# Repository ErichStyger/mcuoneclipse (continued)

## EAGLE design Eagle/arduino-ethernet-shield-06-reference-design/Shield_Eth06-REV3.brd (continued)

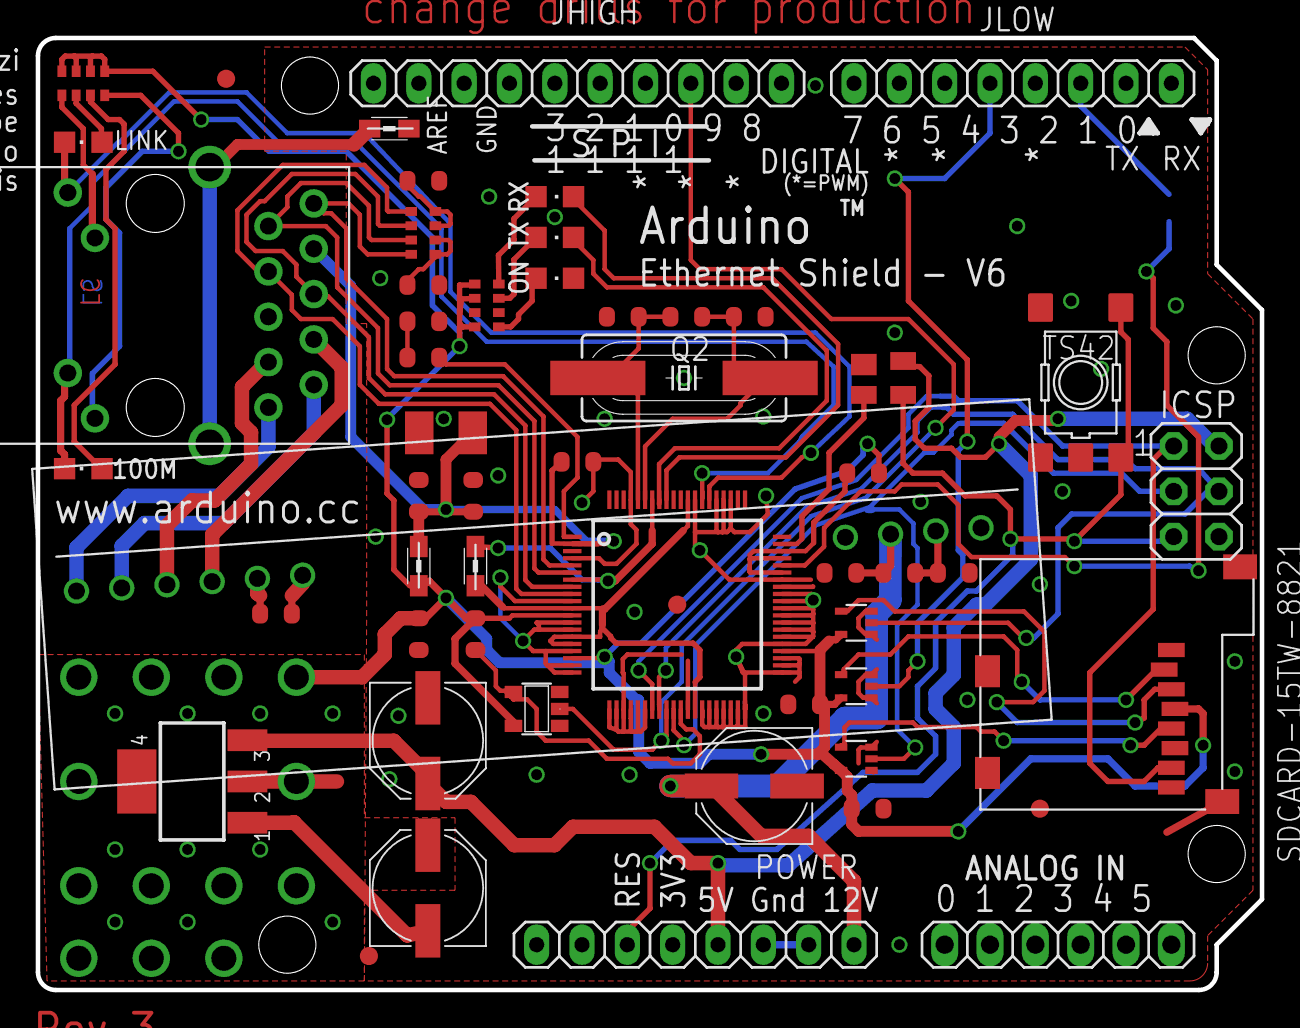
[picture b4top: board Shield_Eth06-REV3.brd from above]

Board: 2 copper layers, 68.6 x 53.3 mm, 57 parts (1 on the bottom side), 50 nets.

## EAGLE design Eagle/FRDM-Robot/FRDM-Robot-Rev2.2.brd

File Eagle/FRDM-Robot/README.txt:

Freedom Robot Board Rev. 2.2
============================

- Schema Änderungen:
  - Ultraschall Speisung auf 5V
  - Bluetooth TX/RX korrigiert

- Änderungen im Layout NICHT GEROUTET!!!

Andrin Tuor, 27.6.2013

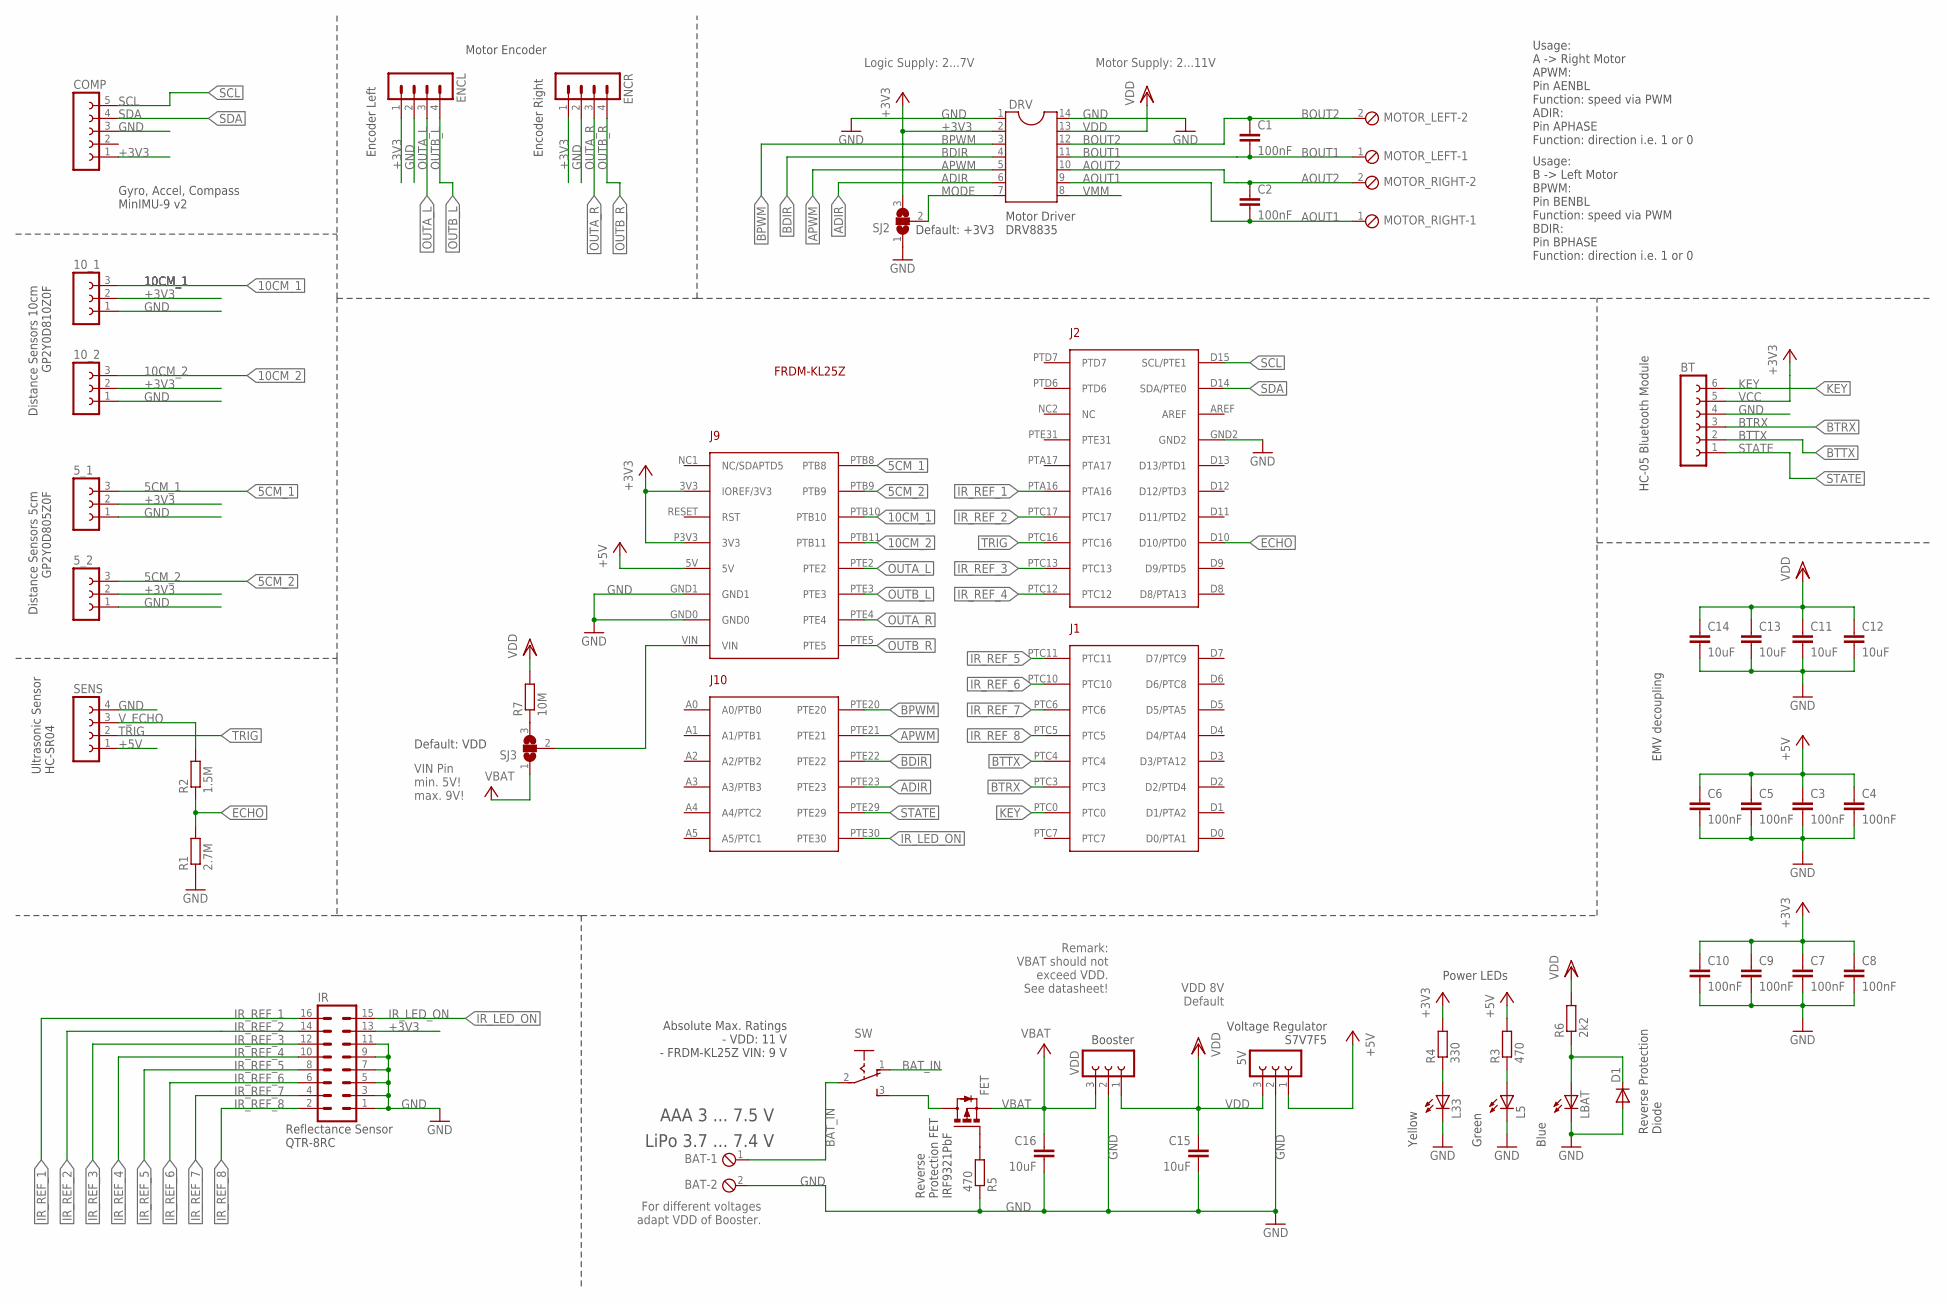
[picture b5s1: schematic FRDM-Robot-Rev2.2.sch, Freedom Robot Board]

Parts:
5V, 5_1, 5_2, 10_1, 10_2: FE03-1
BAT: MPT2; 2POL254
BT: FE06-1; FE06
C1, C2, C3, C4, C5, C6, C7, C8, C9, C10: 100nF; C0805
C11, C12, C13, C14, C15, C16: 10uF; C0805
COMP: FE05-1
D1: DIODE-SOD123; SOD123
DRV: DIL14
ENCL: MA04-1
ENCR: MA04-1
FET: P-MOSFET-SO8; SO-08
FRDM1: FRDM-KL25ZARDUINO; FRDM-KL25Z
IR: MA08-2
L5, L33: LEDCHIP-LED0603; CHIP-LED0603
LBAT: LEDCHIP-LED0603; CHIP-LED0603
MOTOR_LEFT: MPT2; 2POL254
MOTOR_RIGHT: MPT2; 2POL254
R1: 2.7M; M0805
R2: 1.5M; M0805
R3, R5: 470; M0805
R4: 330; M0805
R6: 2k2; M0805
R7: 10M; M0805
SENS: FE04-1
SJ2, SJ3: SJ2W; SJ_2
SW: KNITTER-MFP106D
VDD: FE03-1

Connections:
5CM_1: 5_1.3, FRDM1.PTB8
5CM_2: 5_2.3, FRDM1.PTB9
10CM_1: 10_1.3, FRDM1.PTB10
10CM_2: 10_2.3, FRDM1.PTB11
+3V3: 5_1.2, 5_2.2, 10_1.2, 10_2.2, C7.1, C8.1, C9.1, C10.1, COMP.1, DRV.2, ENCL.1, ENCR.1, FRDM1.3V3 (IOREF/3V3), FRDM1.P3V3 (3V3), IR.13, R4.2, SJ2.3
+5V: 5V.1, C3.1, C4.1, C5.1, C6.1, FRDM1.5V, R3.2, SENS.1
ADIR: DRV.6, FRDM1.PTE23
AOUT1: C2.2, DRV.9, MOTOR_RIGHT.1
AOUT2: C2.1, DRV.10, MOTOR_RIGHT.2
APWM: DRV.5, FRDM1.PTE21
BAT-FET: FET.5 (D), FET.6 (D), FET.7 (D), FET.8 (D), SW.3 (S)
BAT_IN: BAT.1, SW.1 (O), SW.2
BDIR: DRV.4, FRDM1.PTE22
BOUT1: C1.2, DRV.11, MOTOR_LEFT.1
BOUT2: C1.1, DRV.12, MOTOR_LEFT.2
BPWM: DRV.3, FRDM1.PTE20
BTRX: BT.3, FRDM1.PTC3
BTTX: BT.2, FRDM1.PTC4
ECHO: FRDM1.D10 (D10/PTD0), R1.2, R2.1
GND: 5V.2, 5_1.1, 5_2.1, 10_1.1, 10_2.1, BAT.2, BT.4, C3.2, C4.2, C5.2, C6.2, C7.2, C8.2, C9.2, C10.2, C11.2, C12.2, C13.2, C14.2, C15.2, C16.2, COMP.3, D1.A, DRV.1, DRV.14, ENCL.2, ENCR.2, FRDM1.GND0, FRDM1.GND1, FRDM1.GND2, IR.1, IR.3, IR.5, IR.7, IR.9, IR.11, L5.C, L33.C, LBAT.C, R1.1, R5.1, SENS.4, SJ2.1, VDD.2
IR_LED_ON: FRDM1.PTE30, IR.15
IR_REF_1: FRDM1.PTA16, IR.16
IR_REF_2: FRDM1.PTC17, IR.14
IR_REF_3: FRDM1.PTC13, IR.12
IR_REF_4: FRDM1.PTC12, IR.10
IR_REF_5: FRDM1.PTC11, IR.8
IR_REF_6: FRDM1.PTC10, IR.6
IR_REF_7: FRDM1.PTC6, IR.4
IR_REF_8: FRDM1.PTC5, IR.2
KEY: BT.6, FRDM1.PTC0
MODE: DRV.7, SJ2.2
unnamed: L5.A, R3.1
unnamed: R7.1, SJ3.3
unnamed: L33.A, R4.1
unnamed: FET.4 (G), R5.2
unnamed: D1.C, LBAT.A, R6.1
OUTA_L: ENCL.3, FRDM1.PTE2
OUTA_R: ENCR.3, FRDM1.PTE4
OUTB_L: ENCL.4, FRDM1.PTE3
OUTB_R: ENCR.4, FRDM1.PTE5
SCL: COMP.5, FRDM1.D15 (SCL/PTE1)
SDA: COMP.4, FRDM1.D14 (SDA/PTE0)
STATE: BT.1, FRDM1.PTE29
TRIG: FRDM1.PTC16, SENS.2
VBAT: C16.1, FET.1 (S), FET.2 (S), FET.3 (S), SJ3.1, VDD.3
VCC: BT.5
VDD: 5V.3, C11.1, C12.1, C13.1, C14.1, C15.1, DRV.13, R6.2, R7.2, VDD.1
VIN: FRDM1.VIN, SJ3.2
VMM: DRV.8
V_ECHO: R2.2, SENS.3

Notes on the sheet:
Distance Sensors 10cm GP2Y0D810Z0F
Ultrasonic Sensor HC-SR04
Motor Encoder
Motor Driver DRV8835
Reflectance Sensor QTR-8RC
Voltage Regulator S7V7F5
HC-05 Bluetooth Module
Reverse Protection FET IRF9321PbF
LiPo 3.7 ... 7.4 V
Usage: A -> Right Motor APWM: Pin AENBL Function: speed via PWM ADIR: Pin APHASE Function: direction i.e. 1 or 0
Distance Sensors 5cm GP2Y0D805Z0F
EMV decoupling
Power LEDs
Motor Supply: 2...11V
Logic Supply: 2...7V
Remark: VBAT should not exceed VDD. See datasheet!
For different voltages adapt VDD of Booster.
Usage: B -> Left Motor BPWM: Pin BENBL Function: speed via PWM BDIR: Pin BPHASE Function: direction i.e. 1 or 0
Reverse Protection Diode
VIN Pin min. 5V! max. 9V!
VDD 8V Default
Gyro, Accel, Compass MinIMU-9 v2
AAA 3 ... 7.5 V
Absolute Max. Ratings - VDD: 11 V - FRDM-KL25Z VIN: 9 V
Encoder Left
Encoder Right
Booster
Yellow
Green
Blue
Default: +3V3
Default: VDD

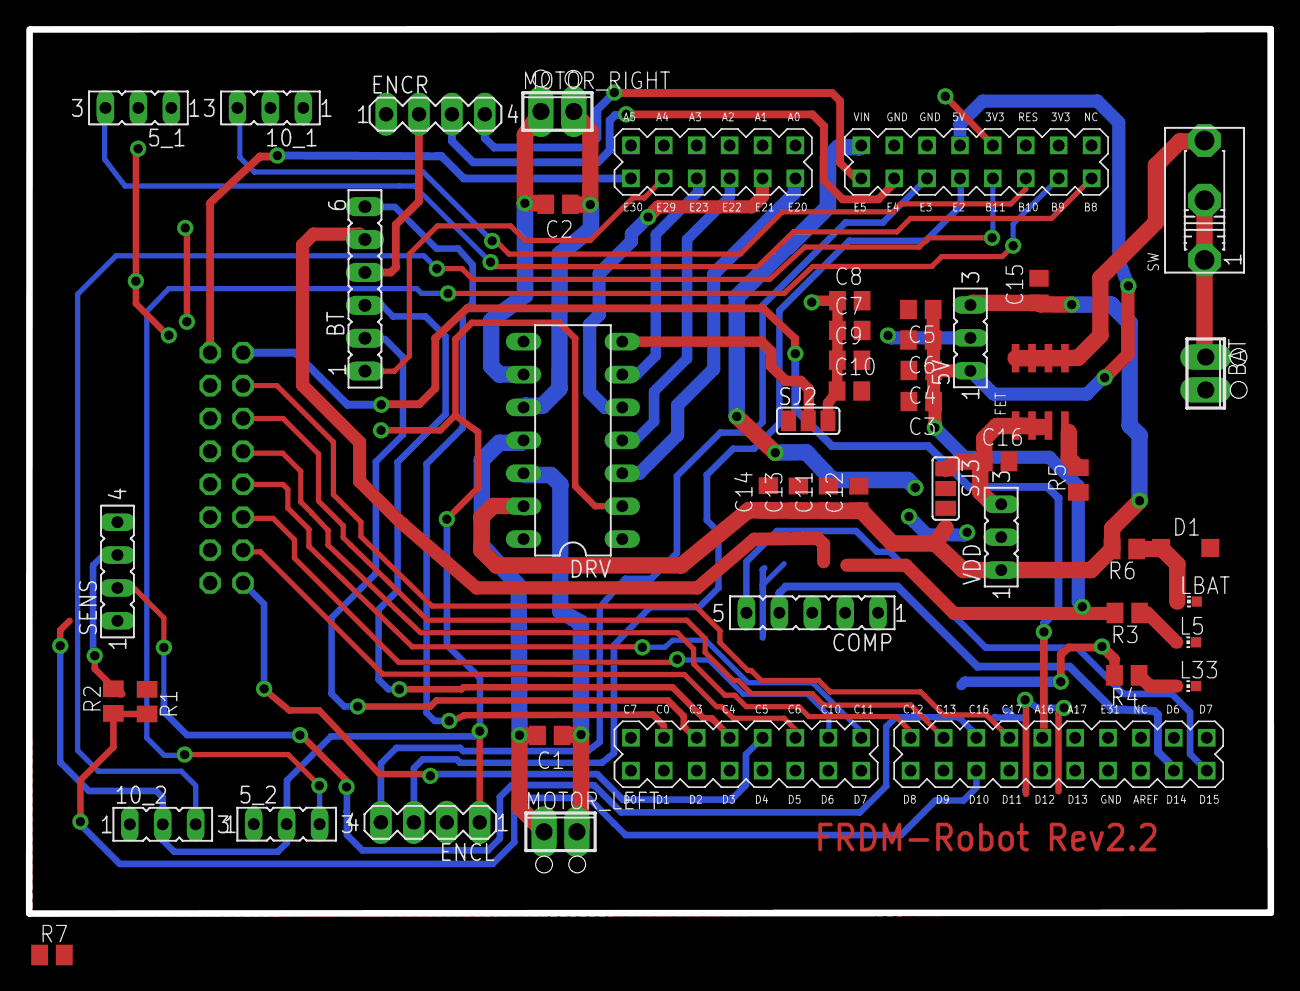
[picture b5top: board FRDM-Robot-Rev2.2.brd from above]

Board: 2 copper layers, 95.8 x 68.3 mm, 48 parts (1 on the bottom side), 48 nets.

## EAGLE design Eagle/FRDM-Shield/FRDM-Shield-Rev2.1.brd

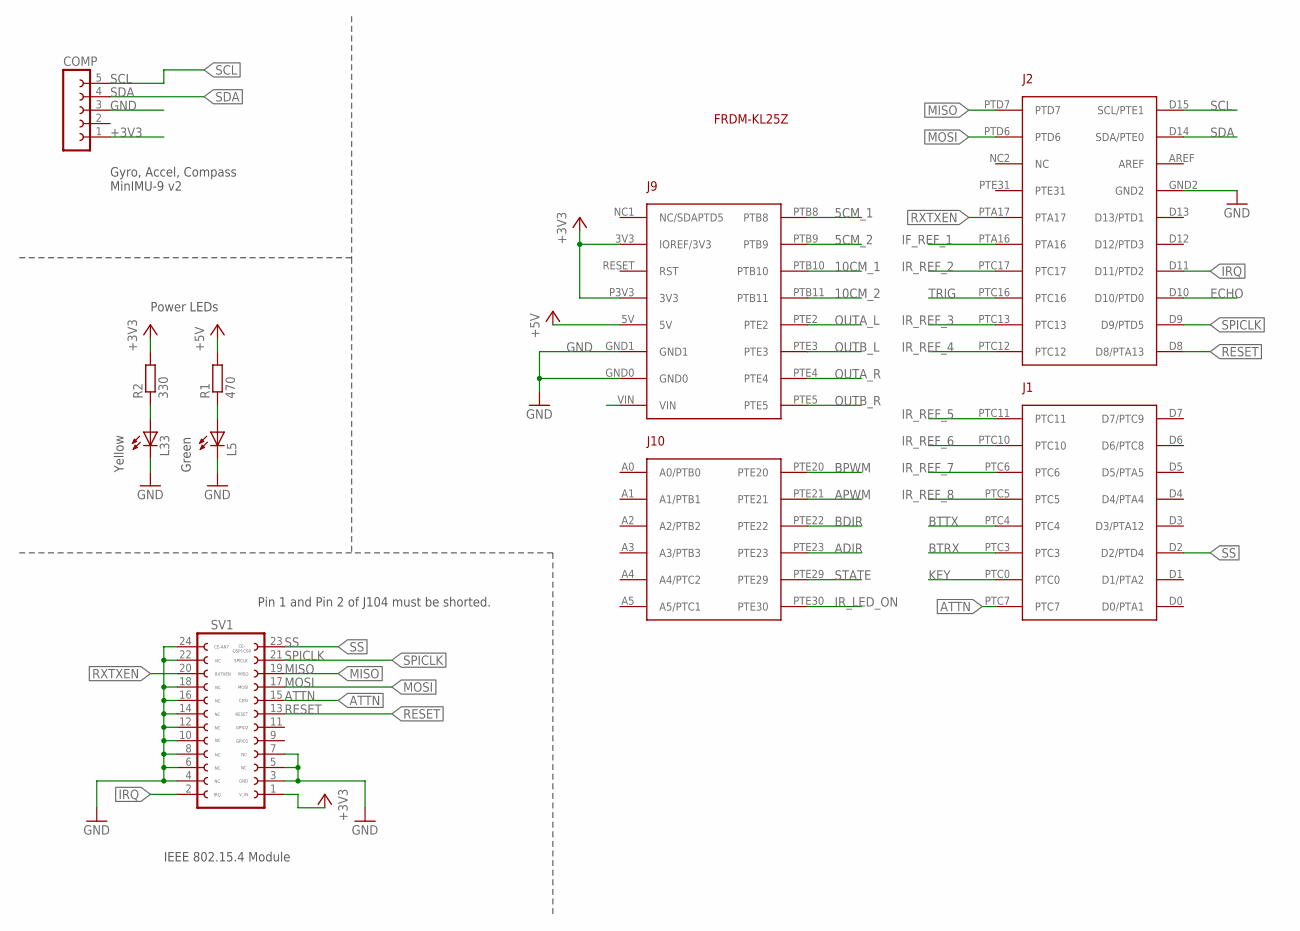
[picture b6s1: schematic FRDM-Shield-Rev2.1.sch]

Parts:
COMP: FE05-1
FRDM1: FRDM-KL25ZARDUINO; FRDM-KL25Z
L5, L33: LEDCHIP-LED0603; CHIP-LED0603
R1: 470; M0805
R2: 330; M0805
SV1: MC1320X; FE12-2

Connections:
5CM_1: FRDM1.PTB8
5CM_2: FRDM1.PTB9
10CM_1: FRDM1.PTB10
10CM_2: FRDM1.PTB11
+3V3: COMP.1, FRDM1.3V3 (IOREF/3V3), FRDM1.P3V3 (3V3), R2.2, SV1.1
+5V: FRDM1.5V, R1.2
ADIR: FRDM1.PTE23
APWM: FRDM1.PTE21
ATTN: FRDM1.PTC7, SV1.15
BDIR: FRDM1.PTE22
BPWM: FRDM1.PTE20
BTRX: FRDM1.PTC3
BTTX: FRDM1.PTC4
ECHO: FRDM1.D10 (D10/PTD0)
GND: COMP.3, FRDM1.GND0, FRDM1.GND1, FRDM1.GND2, L5.C, L33.C, SV1.3, SV1.4, SV1.5, SV1.6, SV1.7, SV1.8, SV1.10, SV1.12, SV1.14, SV1.16, SV1.18, SV1.22, SV1.24
IF_REF_1: FRDM1.PTA16
IRQ: FRDM1.D11 (D11/PTD2), SV1.2
IR_LED_ON: FRDM1.PTE30
IR_REF_2: FRDM1.PTC17
IR_REF_3: FRDM1.PTC13
IR_REF_4: FRDM1.PTC12
IR_REF_5: FRDM1.PTC11
IR_REF_6: FRDM1.PTC10
IR_REF_7: FRDM1.PTC6
IR_REF_8: FRDM1.PTC5
KEY: FRDM1.PTC0
MISO: FRDM1.PTD7, SV1.19
MOSI: FRDM1.PTD6, SV1.17
unnamed: L5.A, R1.1
unnamed: L33.A, R2.1
OUTA_L: FRDM1.PTE2
OUTA_R: FRDM1.PTE4
OUTB_L: FRDM1.PTE3
OUTB_R: FRDM1.PTE5
RESET: FRDM1.D8 (D8/PTA13), SV1.13
RXTXEN: FRDM1.PTA17, SV1.20
SCL: COMP.5, FRDM1.D15 (SCL/PTE1)
SDA: COMP.4, FRDM1.D14 (SDA/PTE0)
SPICLK: FRDM1.D9 (D9/PTD5), SV1.21
SS: FRDM1.D2 (D2/PTD4), SV1.23
STATE: FRDM1.PTE29
TRIG: FRDM1.PTC16

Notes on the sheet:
IEEE 802.15.4 Module
Power LEDs
Pin 1 and Pin 2 of J104 must be shorted.
Yellow
Green
Gyro, Accel, Compass MinIMU-9 v2

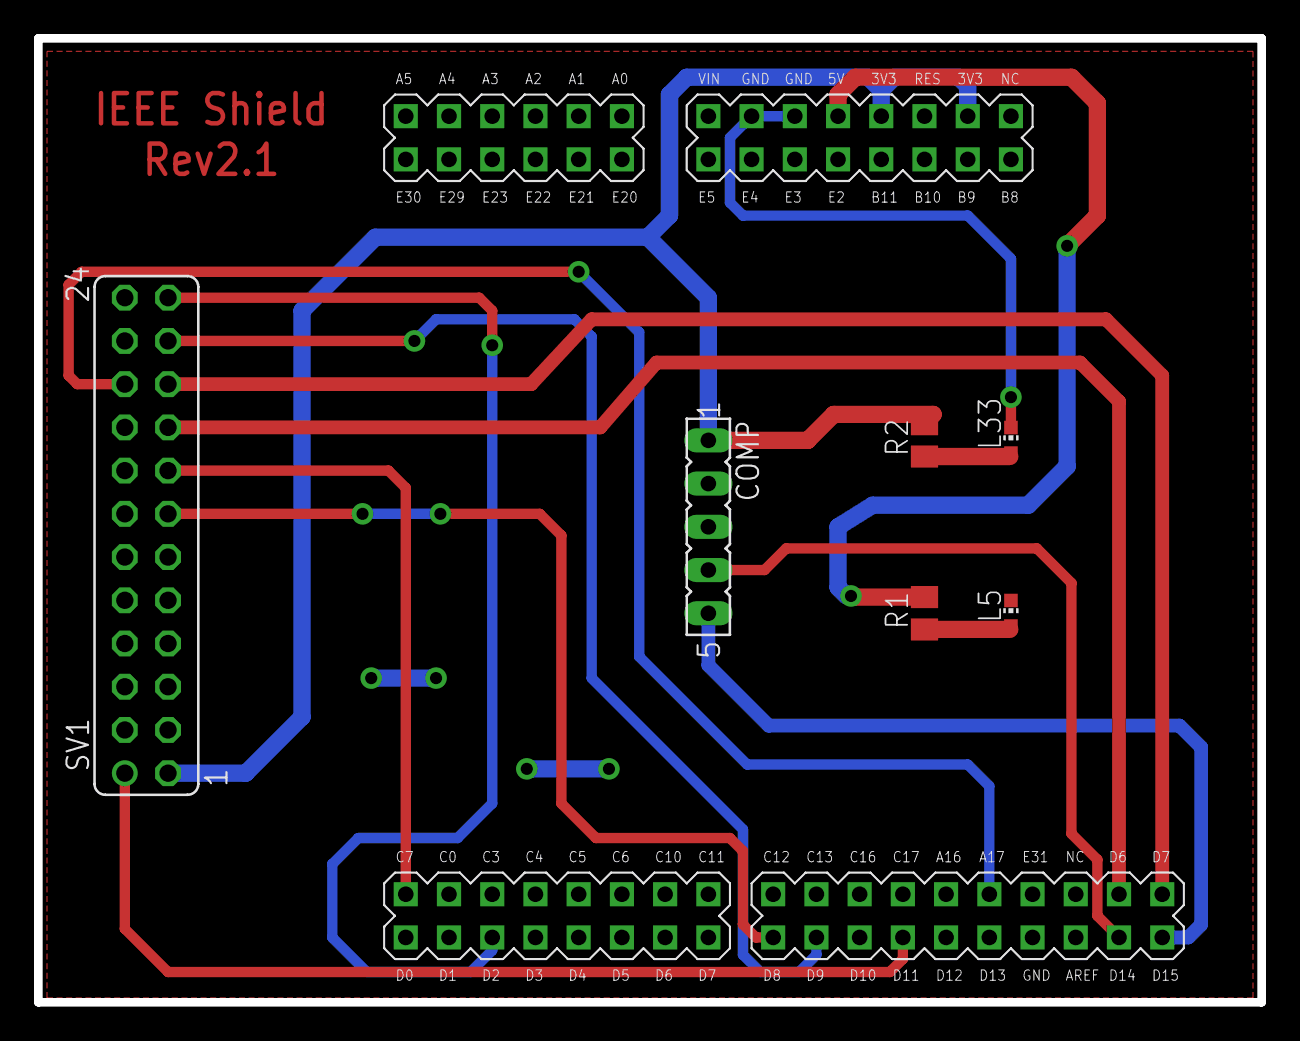
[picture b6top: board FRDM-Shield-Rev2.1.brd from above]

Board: 2 copper layers, 72.1 x 56.6 mm, 7 parts (0 on the bottom side), 15 nets.

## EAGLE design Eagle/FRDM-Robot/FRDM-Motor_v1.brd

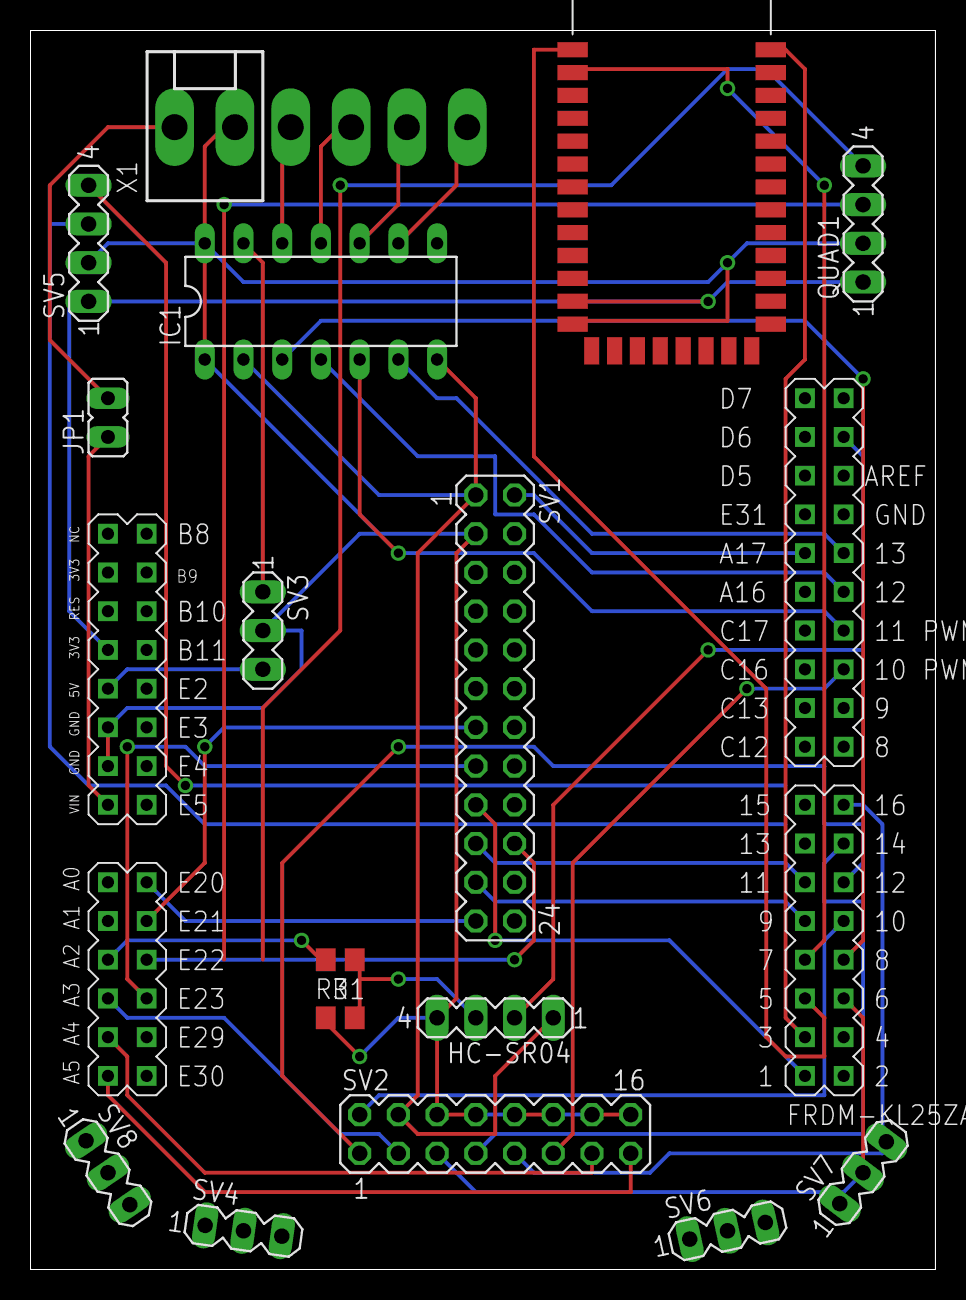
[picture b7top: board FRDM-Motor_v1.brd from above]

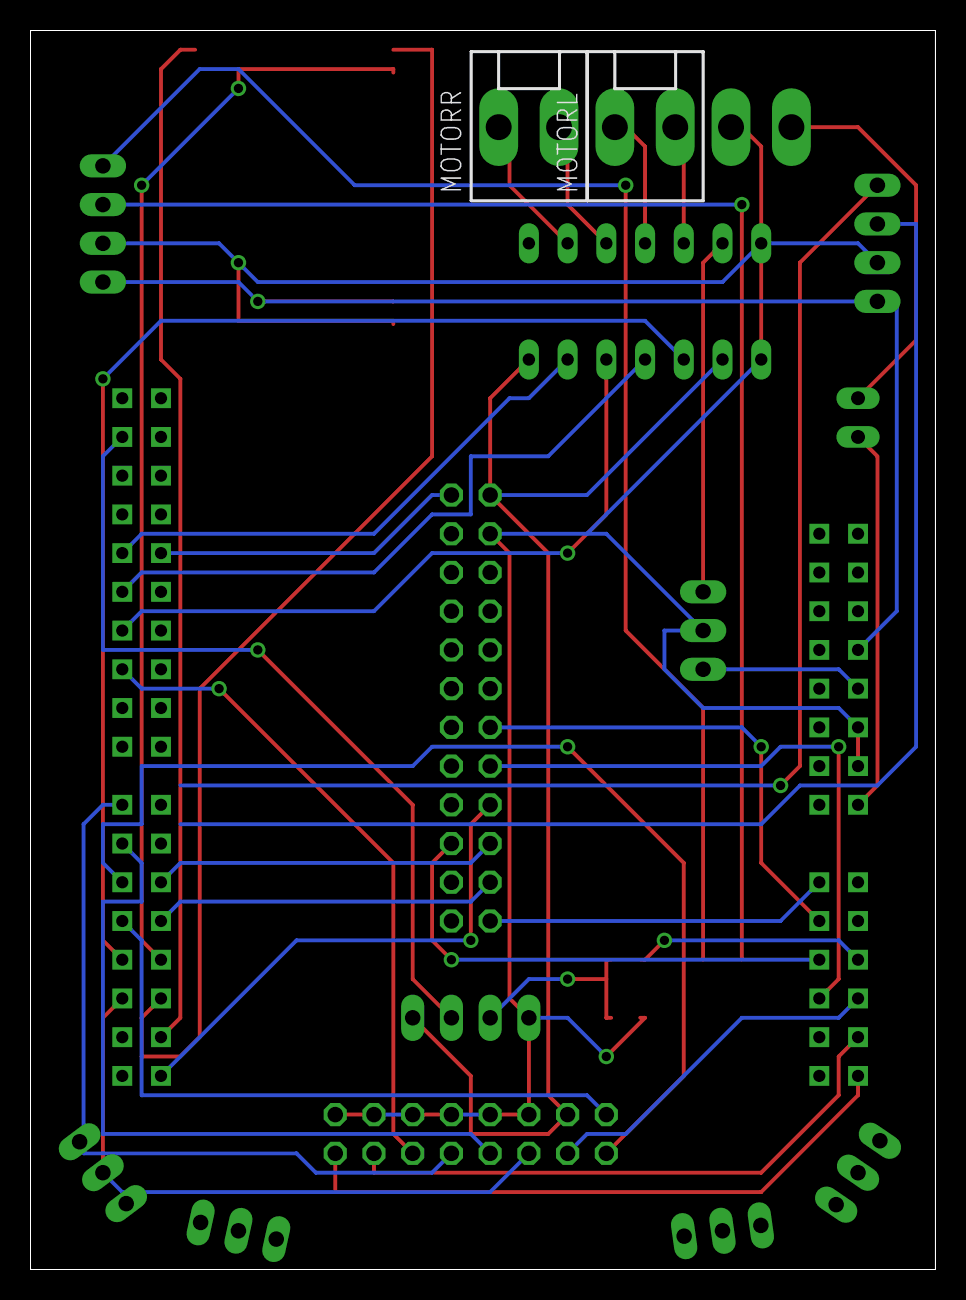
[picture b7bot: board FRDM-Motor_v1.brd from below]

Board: 2 copper layers, 59.4 x 81.3 mm, 19 parts (2 on the bottom side), 46 nets.

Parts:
FRDM1: FRDM-KL25ZARDUINO; FRDM-KL25Z
HC-SR04: SR04; MA04-1
IC1: DRV8835; DIL14
JP1: PWR; JP1
MOTORL: Left; KK-156-2
MOTORR: Right; KK-156-2
QUAD1: QUAD1; MA04-1
R1: 27k; R0805
R3: 15k; R0805
SV1: Radio; MA12-2
SV2: IR; MA08-2
SV3: S7V7F5; MA03-1
SV4, SV6: 10cm; MA03-1
SV5: QUAD2; MA04-1
SV7, SV8: 5cm; MA03-1
U1: HC_05; BLUETOOTH_SMD
X1: Bat; KK-156-2

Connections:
3V3: FRDM1.P3V3, QUAD1.1, SV4.2, SV5.1, SV6.2, SV7.2, SV8.2, U1.12
5CM1: FRDM1.PTE29, SV8.3
5CM2: FRDM1.PTE30, SV7.3
5V: FRDM1.5V, SV3.3
10CM1: FRDM1.PTC10, SV6.3
10CM2: FRDM1.PTC11, SV4.3
AOUT1: IC1.9, MOTORR.1
AOUT2: IC1.10, MOTORR.2
BAT: JP1.2, X1.1
BOUT1: IC1.11, MOTORL.1
BOUT2: IC1.12, MOTORL.2
BTCMD: FRDM1.PTC0, U1.34
BTRX: FRDM1.PTC4, U1.2
BTTX: FRDM1.PTC3, U1.1
C11: FRDM1.PTE2, QUAD1.3
C12: FRDM1.PTE3, QUAD1.4
C21: FRDM1.PTE4, SV5.3
C22: FRDM1.PTE5, SV5.4
DIRL: FRDM1.D12, IC1.4
DIRR: FRDM1.D13, IC1.6
ECHO: FRDM1.A2, R3.2
GND: FRDM1.GND0, FRDM1.GND1, HC-SR04.4, IC1.1, IC1.14, QUAD1.2, R1.1, SV1.3, SV2.6, SV2.8, SV2.10, SV2.12, SV2.14, SV2.16, SV3.2, SV4.1, SV5.2, SV6.1, SV7.1, SV8.1, U1.13, X1.2
IR1: FRDM1.D5, SV2.1
IR2: FRDM1.A3, SV2.3
IR3: FRDM1.D2, SV2.5
IR4: FRDM1.D6, SV2.7
IR5: FRDM1.D7, SV2.9
IR6: FRDM1.D10, SV2.11
IR7: FRDM1.A4, SV2.13
IR8: FRDM1.A5, SV2.15
IR_LED: FRDM1.D4, SV2.2
PWML: FRDM1.D3, IC1.3
PWMR: FRDM1.D11, IC1.5
RADIO_ATTN: FRDM1.PTE23, SV1.15
RADIO_CS: FRDM1.PTE20, SV1.23
RADIO_IRQ: FRDM1.PTA17, SV1.2
RADIO_MISO: FRDM1.PTC6, SV1.19
RADIO_MOSI: FRDM1.PTC7, SV1.17
RADIO_RES: FRDM1.PTE21, SV1.13
RADIO_RTXEN: FRDM1.PTE22, SV1.20
RADIO_SPICLK: FRDM1.PTC5, SV1.21
TRIG: FRDM1.D14, HC-SR04.2
UECHO: HC-SR04.3, R1.2, R3.1
VBAT: FRDM1.VIN, JP1.1
VCC: HC-SR04.1, IC1.2, IC1.7, SV1.1, SV2.4
VIN: IC1.13, SV3.1

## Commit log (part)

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2024-01-26 updated projects
2024-01-28 added particle animation
2024-01-28 updated with latest components
2024-01-28 more updates to latest components
2024-01-29 added heap protector
2024-01-29 updated animation
2024-01-29 added burst, not impleented yet
2024-02-06 updated with latests SDK
2024-02-21 updated version number
2024-02-21 added animation
2024-02-22 updated to latest IDE, moved to CMake Presets
2024-03-07 fixed include header file name
2024-03-07 added more spacer
2024-03-07 fixed header file name
2024-03-07 added SDK internal RTC
2024-03-08 disabled unused function
2024-03-11 making it generic
2024-03-11 fixed name spelling
2024-03-11 updated SDK
2024-03-11 added new font
2024-03-11 fixed typo
2024-03-12 fixed folder spellng for LInux
2024-03-12 added MCU-Link components
2024-03-12 updated project
2024-03-12 updated symbol library
2024-03-15 added clock functionality
2024-03-21 updated flip-dot project
2024-03-23 updated KiCad models and library
2024-03-24 updated symbols and added 3D models
2024-03-24 updated thermal pad
2024-03-24 fixed warnings
2024-03-24 new symbols
2024-04-06 enabled watchdog timer
2024-04-06 updates for business card project
2024-04-12 footprint changed for 6/6 mil
2024-04-17 UID for LPC804
2024-04-17 merged fix for STM32
2024-04-23 added new footprint for TDK VLCF024
2024-04-23 extended support for LPC804
2024-04-24 updated footprints
2024-04-24 added 3D models
2024-04-27 updated projects with using the CMSIS-Core library.
2024-05-05 disabled for Heap3
2024-05-05 turned on BLE
2024-05-05 fix for subcommands > 256
2024-05-05 upgraded LittleFS
2024-05-07 moved from AEMBS project
2024-05-07 fixed readme
2024-05-16 fixed FreeRTOS warnings
2024-05-16 fixed status output
2024-05-16 updated with new IDE and SDK
2024-05-16 new board with 16 LEDs, updated LED animation
2024-05-16 merged with latest git version
2024-05-17 updated year
2024-05-19 updated for latest SDKs
2024-05-19 merged McuLib
2024-05-21 added LPC804 low power example
2024-05-22 updated settings and added link to article
2024-05-22 cleaned project
2024-05-31 updated projects with SDK
2024-05-31 added setting for LED
2024-06-11 fixed handling of event bits
2024-06-13 updated footprints for 0.22mm gap between pads for black soldermask
2024-06-13 updated for 11.9.1
2024-06-13 updated for IDE 11.9.1
2024-06-13 added SDK RT685 project
2024-06-13 working debug session
2024-06-13 updated with config tools
2024-06-13 added pyOCD launch config
2024-06-13 using McuLib
2024-06-13 added patched DFP file
2024-06-19 added ESA demo mode
2024-06-19 added comments
2024-06-21 added option for retargeting
2024-06-21 fixed compiler warning
2024-06-21 updated gcov examples with latest IDE and SDK
2024-06-26 less power for ESA demo
2024-06-29 enabled for C++
2024-06-30 added hardware part
2024-06-30 added 3D printing files
2024-07-01 updated RTC driver
2024-07-03 improved RTC driver
2024-07-03 fixed CMSIS naming of ISRs for RP2040
2024-07-05 improved animation
2024-07-10 updated for linux usage
2024-07-10 cleanup
2024-07-23 updated projects with new IDE
2024-07-24 updated USB stack
2024-07-24 updated mex
2024-07-24 updated projects with new SDKs
2024-07-24 removed part support
2024-07-24 updated coverage and projects
2024-07-24 GPIO and LED support for MCX (N947)
2024-07-24 added MCX project
2024-07-29 changed to newlib-nano
2024-07-29 added sdk project
2024-07-29 updated McuLib for MCX
2024-07-31 added standalone cov converter
2024-08-02 need to align FreeRTOS information struct for LinkServer debugging at higher gcc optimizations.
2024-08-02 upcated gcov implementation
2024-08-02 updated projects with new IDE and SDK
2024-08-02 using OLED without GUI
2024-08-08 updated with new components
2024-08-15 project cleanup, verified bm gcov with K64
2024-08-15 added LEDs
2024-08-15 undo temporary change
2024-08-15 added GPIO release and NeoPixels for Raspy Interface
2024-08-16 using latest gcc
2024-08-16 updated for gcc13
2024-08-16 initial C++ project
2024-08-16 moved to IDE 11
2024-08-16 added McuLib
2024-08-16 added C++ interface
2024-08-16 adding gcov support
2024-08-17 added blinky
2024-08-17 fixed include order for i.MX
2024-08-17 added MEX
2024-08-17 cleanup and added link to article.
2024-08-23 updated configurations
2024-08-25 added SEGGER SystemView example for Data Plot functionality.
2024-08-26 Updated SystemView to v3.56
2024-08-26 merged with PEx driver
2024-08-27 switching back ot anonymous union
2024-08-27 working with integer: problem was using a scaling factor of zero.
2024-08-27 updated debug probe settings
2024-08-27 added newline
2024-08-27 changed to signed data type
2024-08-27 more more with SEGGER sources
2024-08-27 added Team Project Set
2024-08-28 updated SDK version
2024-08-29 updated launch settings
2024-09-05 using non-anonymous union
2024-09-26 added MCXN236 base project
2024-09-26 working blinky
2024-09-26 added RTT
2024-09-26 add RTT
2024-09-27 cleanup and extended project
2024-09-30 removed freestanding
2024-09-30 updated probe firmware
2024-10-03 updated SDK and probe settings
2024-10-03 initial usb host project
2024-10-03 added usb files
2024-10-04 moved files
2024-10-04 added CMake files
2024-10-04 fixed linking libraries
2024-10-04 working shell
2024-10-04 added board and LED support
2024-10-04 added header
2024-10-04 enabling usb host
2024-10-04 working CDC on device side
2024-10-04 slowed down debug output
2024-10-04 working host mode HID with device CDC
2024-10-14 change for SDK 2.0.0
2024-10-20 updated with latest McuLib
2024-10-22 fixed directory name
2024-10-23 commit added debug output
2024-10-23 working with standard pico board and USB host breakout
2024-10-23 re-added CDC host support
2024-10-23 added exit call
2024-10-23 added CDC host
2024-10-24 added footprint
2024-10-31 fixed format string
2024-11-01 fixed include for sdk 2.0.0
2024-11-01 using tinyk22 USB stack
2024-11-04 adding new module McuShellCdcDevice
2024-11-12 updated launch settings for new McuLink probe
2024-11-18 fixed SDK version
2024-11-20 added picotool windows binary for SDK 2.0.0.
2024-11-24 fixed McuLink location
2024-11-24 udpated debug probe
2024-11-24 updated description
2024-12-04 added new modules
2024-12-06 merged McuLib with new version from master
2024-12-06 removing batch files
2024-12-07 ported project to SDK 2.0.0
2024-12-09 updated with new SDK 2.0.0
2024-12-11 updated McuLib
2024-12-11 using new SDK
2024-12-11 cleanup, not needed anymore
2024-12-14 merged project with sensor project, VS Code only
2024-12-23 Added new animations
2024-12-24 updated launch configs
2024-12-27 Added helicopter and pyramid animation
2025-01-13 added missing include
2025-01-14 added semihosting example
2025-01-14 merged McuLib and updated projects
2025-01-14 updated semihosting
2025-01-15 updated projects and extended documentation
2025-01-15 extended buffer size
2025-01-15 disabled semihosting testing
2025-01-17 added console processing
2025-01-17 extended semihosting for latest LinkServer
2025-01-17 updated with new SDK
2025-01-17 extended semihosting with shell
2025-01-21 initial project
2025-01-22 updated McuLib location
2025-01-22 extended implementation with RNet, RTC and LEDs
2025-01-24 increased stack size
2025-01-24 enabled SWO
2025-01-24 testing SWO output clocking
2025-01-31 added sensor code
2025-02-04 updated SDKs
2025-02-12 added %n handling
2025-02-12 extended comment
2025-02-12 added semihosting prefix handling
2025-02-13 migrating to McuLib sub-repo
2025-02-13 using submodule for McuLib
2025-02-18 changed debug probe
2025-02-27 Updated with latest component versions
2025-02-27 initial project, based on the work of Peter
2025-02-27 converted with 24.12 IDE
2025-02-27 going to ignore that file
2025-02-27 using common McuLib
2025-03-06 updated SDK for secure/non-secure demo
2025-03-10 had to fix launch configs
2025-03-13 added Adafruit Feather project
2025-03-13 added shell support
2025-03-19 using 8 MByte of FLASH
2025-03-19 enabled RTT
2025-03-19 working WS2812B
2025-03-19 disabled normal LED support
2025-03-26 updated symbols
2025-03-26 added nRF and V_AUX support
2025-04-07 added J-Link script
2025-04-07 added standalone SDK project
2025-04-07 cleanup and added readme
2025-04-07 cleanup, fixed flash task
2025-04-07 added git to the list
2025-04-30 changed probe
2025-05-16 added test code for UART2
2025-05-16 muxing extra GPIO pin
2025-05-25 fixed typos
2025-05-25 new version
2025-06-18 added setting for SonarQube
2025-06-18 updated library
2025-06-18 better USB performance
2025-06-18 sending presence detection message
2025-06-30 using new McuLib
2025-07-07 excluded folders for bare-metal mode
2025-07-07 enabled semihosting with file I/O
2025-07-18 added new launch configuration
2025-07-18 added RAM target
2025-07-18 renamed main file
2025-08-10 added top part
2025-08-10 removed freestanding option
2025-08-10 new McuLib
2025-08-11 merged project and updated to latest version
2025-08-25 merged projectes
2025-08-25 added VS Code project for LPC55S69
2025-08-25 enabled application
2025-08-27 updated SDK version information
2025-08-28 adding USB HID project
2025-08-28 updated debug config and working blinky
2025-08-28 added HID example
2025-08-28 added LED blinky
2025-09-01 working USB HID
2025-09-22 cleanup and added environment setup
2025-10-01 added comment
2025-10-01 new McuLib release
2025-10-13 updated SDK and changed debug probe
2025-10-15 updated new debug probe settings
2025-10-15 added standalone Rust Embassy example
2025-10-24 Updated version of McuLib
2025-10-24 added information to readme
2025-10-24 improved USB CDC performance and blocking
2025-10-24 using cortex delay
2025-10-24 run analyzer on save
2025-10-28 updated symbols for KiCad 9.0
2025-10-28 added project using different external power/voltage/current measurement ICs
2025-10-28 fixed title
2025-10-30 updated footprint
2025-10-30 fixed missing include
2025-11-20 added muxing
2025-11-20 disabled test
2025-11-20 adding new driver for GPé8403
2025-11-20 updated header and added config item
2025-11-20 integrated DAC module driver
2025-11-20 disabled automatic data sending
2025-11-26 reflecting DAC
2025-11-26 working I2C communication
2025-11-27 improved swap macro
2025-11-27 added more functionality, but reading always 0x1111 back from device
2025-12-04 extended sensors, work in progress
2025-12-08 improved DAC handling, prepared for multiple devices
2025-12-08 added support for 2 DAC devices
2025-12-08 renamed launch configs
2025-12-08 fixed bit order
2025-12-08 configured device pins
2025-12-08 configured SPI
2025-12-08 reading more registers
2025-12-08 fixed de-init
2025-12-08 added scaling to values
2025-12-08 extended reading functions
2025-12-08 added shunt handling
2025-12-08 extended driver
2025-12-11 moved power measurement project from internal repo
2025-12-23 integrated contribution of Raul Trrpon driving a bistable relais.
2025-12-25 added design files
2025-12-31 updated comments
2025-12-31 improved name plate
2025-12-31 better fit for more recent PCBs
2025-12-31 updated STL files
2026-01-20 added MCU-Link Pro rugged enclosure
2026-01-20 fixed command handling
2026-01-20 enabled RTT shell interface
2026-02-08 updated design files
2026-03-03 added rugged box project
2026-03-03 added lido reader, starting point
2026-03-04 updated lido parsing
2026-03-04 implemented more reading functionality
2026-04-23 updated KiCad symbols
2026-04-23 finished file reader for LiDo dump files
2026-04-23 updated footprint with PCB drills for standoffs
2026-04-23 enabled tracealyzer
2026-04-24 Update README.txt
    added DeepWiki link
2026-05-05 updated 3D files
2026-05-05 trying out Tracealyzer
2026-05-07 fix: V-002 security vulnerability
    Automated security fix generated by Orbis Security AI
2026-05-15 using common WiFi modules
2026-05-26 udpated McuLib
2026-05-26 updated link
